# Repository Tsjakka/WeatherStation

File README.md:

# Weather Station
An ESP32 / Arduino project to create a high-quality sensor unit for use with Fine Offset weather stations

For several years I enjoyed my Alecto 4000 weather station (more commonly known as Fine Offset WH1080). It has a good display and an easy to mount outdoor unit with anemometer and wind direction. I could connect it to my Raspberry Pi so I was able to get weather information over the internet at any time.
The downside of the system is the relatively short lifespan of the outdoor unit. Based on my experience with two systems I estimate it lasts around three years. I also couldn’t attest to the accuracy of wind measurements, because the outdoor unit was mounted on a short pole and will surely have been influenced by its close proximity to the house.
Last year the outdoor unit of my second system got stuck and I started to contemplate an alternative. As it happened, a long time ago I was given a professional anemometer that was struck by lightning and needed to be replaced. I decided that the time had come to give that one a try and see if it still worked and if I could use it in a new, better weather system.

Since the anemometer does not come with a display or anything, I thought about combining the display of the Alecto with the anemometer. I saw basically two paths that I could take; 1. using the original outdoor transmitter and connecting the anemometer by converting its output to something the transmitter can understand or 2. replacing the whole outdoor unit with something else (and preferably better). 

After some failed attempts at solution 1, I decided to go for option 2. Discussing this solution with a friend, I decided to recreate the outdoor unit using the following parts:

* An ESP32 microcontroller
* A Bosch BME280 temperature/pressure/humidity sensor (in 2021 replaced by a Sensirion SHT31 temperature/humidity sensor, because the BME280 was not reliable enough)
* A DCF1 DCF time receiver
* A Hope RMF69HW RF transceiver
* The Thiess 3323.21.002 anemometer
* The original Alecto rain meter

In a schematic:

The first 4 parts are to be housed in the original Alecto housing. The whole thing to be powered by 230V or optionally a solar panel.

The software will be made in the Arduino software development environment. For all these devices Arduino libraries are available, which makes development much easier.

After ordering the parts, I started connecting and integrating the individual devices one by one, using a breadboard. It took many months to integrate all parts into the system, creating both the electrical connections and the software. Especially tricky was getting the RF communication to the Alecto display to work. Although there is quite a lot of info and sample code available on the internet regarding this, all examples involve the opposite way of using it, where the original outdoor sensor is used and the signal is received by another device, such as a Raspberry Pi.

When I had the system running on the breadboard, I started working on a PCB that fits the housing of the Alecto. This turned out to be a lot of work too, since each connection has to be soldered manually. In the Photos directory you can find more images of this.

During this process I lost a lot of time because of a badly soldered connection. This led me to replace the RF chip twice, which didn’t fix it. The problem was that when verifying the connections, I pressed my Ohm meter against the bad connection, which was then shorted. As soon as I removed my Ohm meter the connection became unstable again.

The Arduino software, which can be downloaded from here, contains a lot of software features:

* Reading data from all included sensors (wind direction and -speed, rain, temperature, humidity, pressure and time).
* Calculating aggregated (wind) data using algorithms based on the recommendations of the World Meteorological Society.
* Building the RF packets that are sent to the display.
* Sending the data packets over RF every 48 seconds.
* Over the air (OTA) updating of the software.

Also the OTA functionality turned out to be tricky. One of the problems was that you cannot use certain GPIO when using the WiFi functionality of the ESP32. Refer to [RandomNerdTutorials](https://randomnerdtutorials.com/esp32-pinout-reference-gpios/) for a lot of info on connecting peripherals to the ESP32. The result was that I had to resolder several connections. Because I could not do that for the GPIOs used for the anemometer, I decided to turn on the WiFi connection only after rebooting the ESP32 twice within 20 seconds. Another issue is that WiFi reception is considerably worse when the ESP32 is connected to the PCB.

In the end, I got everything working properly. Here you can see the weather station in action:

Although it was frustrating at times, I enjoyed this project as a creative and learning experience. The results can be seen on my weather site, http://www.blixemboschweer.nl. I hope some of you will make use of the results, perhaps even by building your own weather station. Please report on your experience if you can.

Greetings,
Tsjakka

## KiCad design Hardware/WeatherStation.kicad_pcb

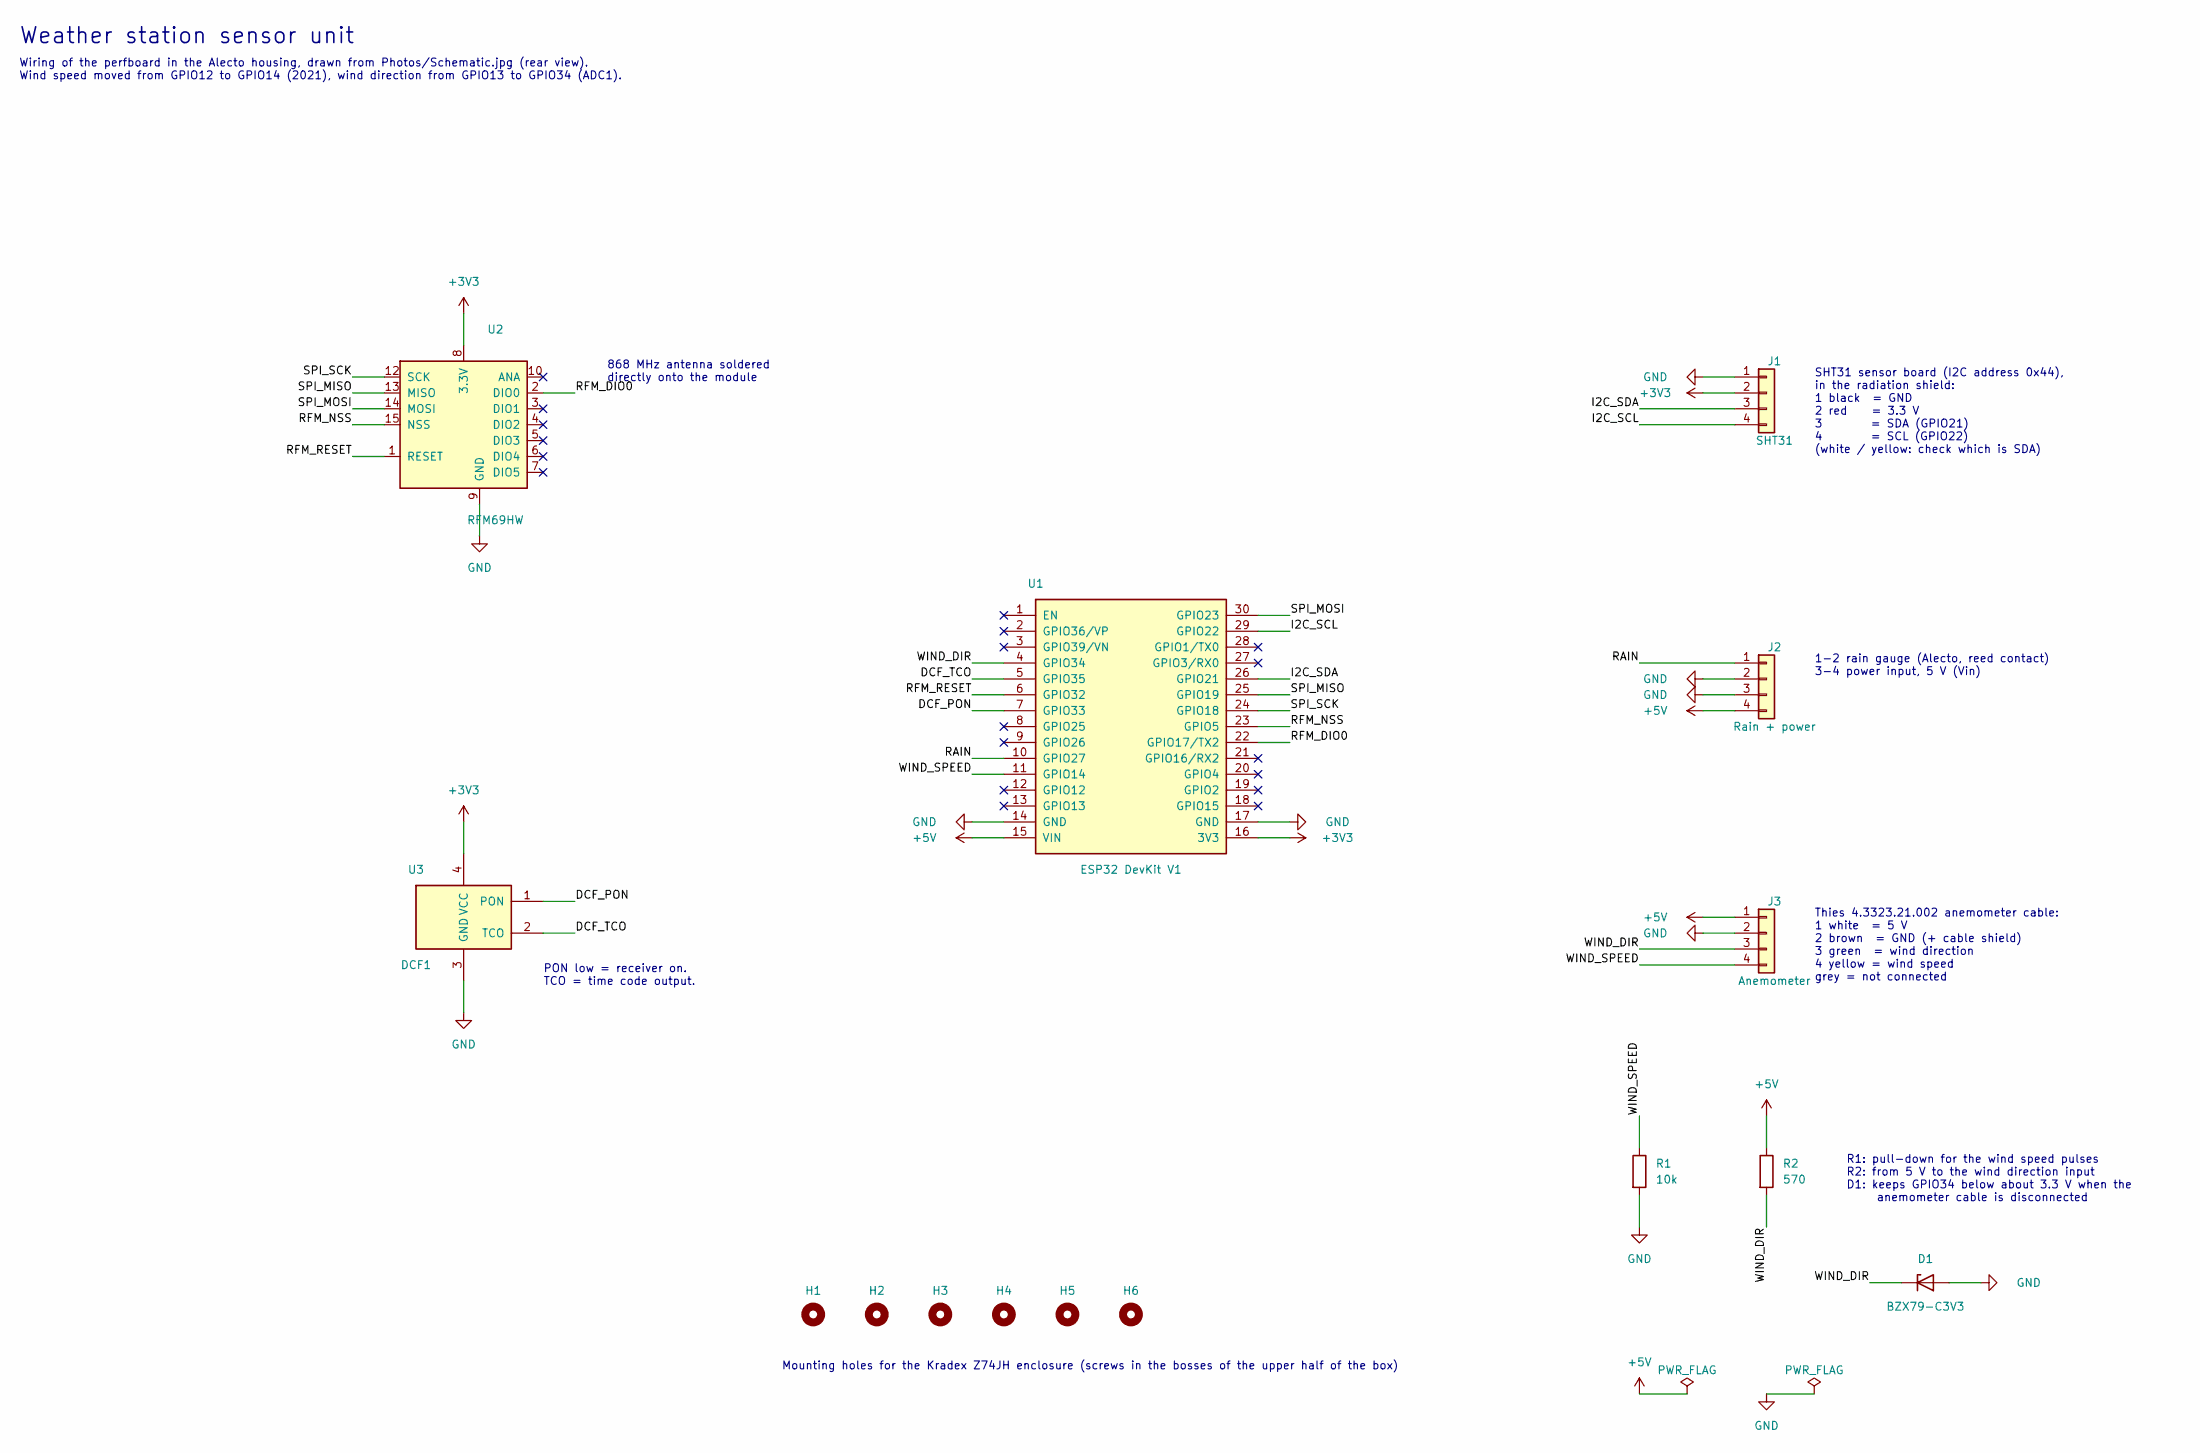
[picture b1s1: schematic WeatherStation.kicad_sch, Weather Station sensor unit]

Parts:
D1: BZX79-C3V3; D_DO-35_SOD27_P7.62mm_Horizontal
H1, H2, H3, H4, H5, H6: MountingHole; MountingHole_3.2mm_M3
J1: SHT31; PhoenixContact_MSTBA_2,5_4-G-5,08_1x04_P5.08mm_Horizontal
J2: Rain + power; PhoenixContact_MSTBA_2,5_4-G-5,08_1x04_P5.08mm_Horizontal
J3: Anemometer; PhoenixContact_MSTBA_2,5_4-G-5,08_1x04_P5.08mm_Horizontal
R1: 10k; R_Axial_DIN0207_L6.3mm_D2.5mm_P10.16mm_Horizontal
R2: 570; R_Axial_DIN0207_L6.3mm_D2.5mm_P10.16mm_Horizontal
U1: ESP32 DevKit V1; ESP32_DevKit_30_Socket
U2: RFM69HW; RFM69HW_Socket_2.00mm
U3: DCF1; PinSocket_1x04_P2.54mm_Vertical

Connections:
+3V3: J1.2, U1.16 (3V3), U2.8 (3.3V), U3.4 (VCC)
+5V: J2.4, J3.1, R2.1, U1.15 (VIN)
/DCF_PON: U1.7 (GPIO33), U3.1 (PON)
/DCF_TCO: U1.5 (GPIO35), U3.2 (TCO)
/I2C_SCL: J1.4, U1.29 (GPIO22)
/I2C_SDA: J1.3, U1.26 (GPIO21)
/RAIN: J2.1, U1.10 (GPIO27)
/RFM_DIO0: U1.22 (GPIO17/TX2), U2.2 (DIO0)
/RFM_NSS: U1.23 (GPIO5), U2.15 (NSS)
/RFM_RESET: U1.6 (GPIO32), U2.1 (RESET)
/SPI_MISO: U1.25 (GPIO19), U2.13 (MISO)
/SPI_MOSI: U1.30 (GPIO23), U2.14 (MOSI)
/SPI_SCK: U1.24 (GPIO18), U2.12 (SCK)
/WIND_DIR: D1.1 (K), J3.3, R2.2, U1.4 (GPIO34)
/WIND_SPEED: J3.4, R1.1, U1.11 (GPIO14)
GND: D1.2 (A), J1.1, J2.2, J2.3, J3.2, R1.2, U1.14 (GND), U1.17 (GND), U2.9 (GND), U2.11 (GND), U3.3 (GND)

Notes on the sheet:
868 MHz antenna soldered directly onto the module
Weather station sensor unit
PON low = receiver on. TCO = time code output.
R1: pull-down for the wind speed pulses R2: from 5 V to the wind direction input D1: keeps GPIO34 below about 3.3 V when the anemometer cable is disconnected
1-2 rain gauge (Alecto, reed contact) 3-4 power input, 5 V (Vin)
SHT31 sensor board (I2C address 0x44), in the radiation shield: 1 black = GND 2 red = 3.3 V 3 = SDA (GPIO21) 4 = SCL (GPIO22) (white / yellow: check which is SDA)
Thies 4.3323.21.002 anemometer cable: 1 white = 5 V 2 brown = GND (+ cable shield) 3 green = wind direction 4 yellow = wind speed grey = not connected
Wiring of the perfboard in the Alecto housing, drawn from Photos/Schematic.jpg (rear view). Wind speed moved from GPIO12 to GPIO14 (2021), wind direction from GPIO13 to GPIO34 (ADC1).
Mounting holes for the Kradex Z74JH enclosure (screws in the bosses of the upper half of the box)

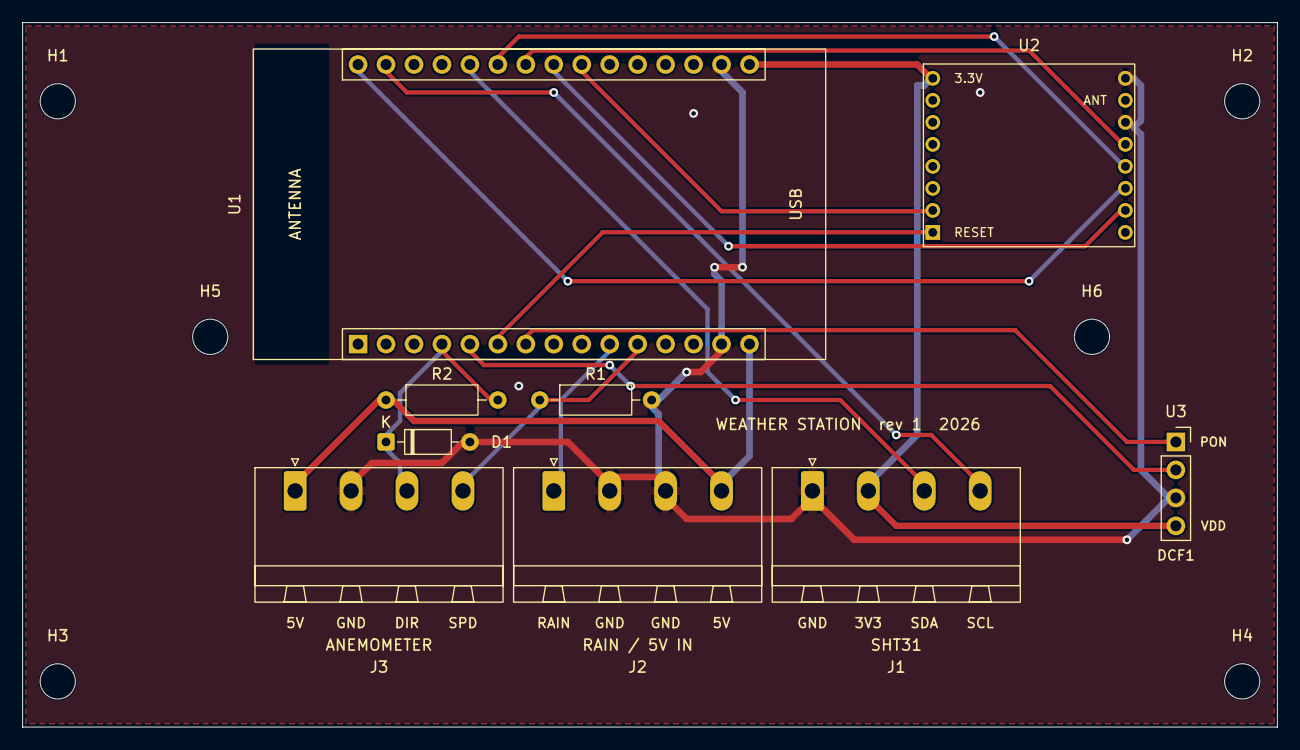
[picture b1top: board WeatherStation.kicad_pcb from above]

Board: 2 copper layers, 114.0 x 64.0 mm, 15 parts (0 on the bottom side), 16 nets.

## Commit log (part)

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2020-01-03 Create dummy
2020-01-03 Add source files
2020-01-03 Add schematic
2020-01-21 Removed some files.
2020-01-21 Added missing files.
2020-02-18 Fix for negative temperatures. Smaller wind speed buffer to prevent averaging by both ESP and base station.
2020-04-17 Updated photo.
2020-05-01 Wind direction buffer shortened to 48s. Fixes to direction and temperature calculation. Shows number of boots on OTA html page.
2021-05-02 Replaced BME280 by SHT31, because of lackluster reliability. Cleaned up #include's. Changed wind speed pin from 12 to 14.
2022-09-18 Improved rain detection.
